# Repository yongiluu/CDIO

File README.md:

# Proyecto CDIO - Sistema de Mando y Control de Vehículo Autónomo / RC

Este repositorio contiene la arquitectura completa de hardware y software para el sistema de control remoto y telemetría de un prototipo vehicular desarrollado bajo la metodología **CDIO** (*Conceive, Design, Implement, Operate*).

El sistema se basa en una arquitectura maestro-esclavo (transmisor-receptor) bidireccional punto a punto (P2P) utilizando dos microcontroladores **ESP32** comunicados mediante el protocolo de baja latencia **ESP-NOW**.

---

## 🚀 Arquitectura General del Sistema

El proyecto está modularizado en dos bloques principales:

```
                  ┌──────────────────────┐
                  │   TRANSMISOR (TX)    │
                  │ (Estación / Control) │
                  └──────────┬───────────┘
                             │  ESP-NOW (WiFi P2P 2.4 GHz)
                             │  Baja Latencia (< 5 ms)
                             ▼
                  ┌──────────────────────┐
                  │    RECEPTOR (RX)     │
                  │   (Vehículo / Auto)  │
                  └──────────┬───────────┘
            ┌────────────────┴────────────────┐
            ▼                                 ▼
   ┌─────────────────┐               ┌─────────────────┐
   │ Servo Dirección │               │  Puente H 43A   │
   │  (Ángulo Turn)  │               │   (BTS7960)     │
   └─────────────────┘               └────────┬────────┘
                                              ▼
                                     ┌─────────────────┐
                                     │  Motor Tracción │
                                     └─────────────────┘
```

1. **`transmisor_TX/` (Estación de Mando / Control Remoto):**
   - Lectura analógica de Joysticks (resolución de 12 bits: `0 - 4095`).
   - Algoritmo de filtrado con **Zona Muerta (Deadzone)** para compensar deriva física (*drift*).
   - Empaquetado de datos en estructura `MensajeDatos` y despacho periódico a alta frecuencia (20 Hz / cada 50 ms).

2. **`receptor_RX/` (Vehículo / Actuadores):**
   - Recepción en tiempo real de paquetes vía callback asíncrono de ESP-NOW.
   - Control de ángulo para servomotor de dirección (`ESP32Servo`, Pin 13).
   - Control de velocidad y sentido de tracción mediante Puente H de alta potencia **BTS7960** (Pines 25, 26 y 27) utilizando canales PWM por hardware (`ledc`).
   - Sistema *Failsafe* (apagado del puente H en reposo para evitar consumo y movimientos involuntarios).

---

## 🛠️ Especificaciones de Hardware y Pines

### 1. Receptor (RX - Vehículo)
* **Microcontrolador:** ESP32-WROOM-32 (esp32dev).
* **Controlador de Tracción:** BTS7960 (43A H-Bridge).
  * `PIN_RPWM` -> **GPIO 25** (Canal PWM 0)
  * `PIN_LPWM` -> **GPIO 26** (Canal PWM 1)
  * `PIN_EN` (R_EN y L_EN unificados) -> **GPIO 27**
  * Potencia limitada a **50 % de PWM** (`PWM_MAX_PCT` en `receptor_RX/src/main.cpp`): el stick a fondo entrega 127 de 255, porque el motor 540 es de 7,2 V y la LiPo 3S llega a 12,6 V.
* **Servomotor de Dirección:** SG90 / MG996R (50 Hz).
  * `PIN_SERVO_DIR` -> **GPIO 13**
* **Sistema de Alimentación:**
  * Batería LiPo 2S/3S conectada a la etapa de potencia del BTS7960 (`B+` y `B-`).
  * Regulador Step-Down DC-DC **LM2596** reduciendo voltaje a 5.0V para alimentar el ESP32 (pin `VIN`/`5V`), el servo y la lógica del BTS7960.
  * Tierras comunes (**GND**) compartidas en un único punto de referencia.

### 2. Transmisor (TX - Control Remoto)
* **Microcontrolador:** ESP32-WROOM-32 (esp32dev).
* **Mando Analógico:** 2 Joysticks analógicos de dos ejes.
  * Eje Y (Velocidad / Tracción) -> **GPIO 34**
  * Eje X (Dirección / Ángulo) -> **GPIO 35**
  * Botón del stick de potencia (*fast brake*) -> **GPIO 25** (pull-down: el otro lado del botón a 3,3 V)
* **Filtrado de Señal:**
  * Rango muerto calibrado entre `1400` y `2000` cuentas ADC para asegurar que el centro físico repose en `Velocidad = 0` y `Ángulo = 90°`.

---

## 📦 Estructura de Datos (ESP-NOW)

Ambas placas intercambian la estructura binaria exacta:

```cpp
typedef struct MensajeDatos {
    int clave;     // 0xCD10: el RX descarta paquetes de otros dispositivos ESP-NOW
    int velocidad; // Rango: -255 a 255 (0 = detenido, >0 = adelante, <0 = reversa)
    int angulo;    // Rango: -38° a +38° del servo respecto al centro (0 = recto; centro en 50°, servo de 12° a 88°)
    int freno;     // 1 = fast brake (click en el stick de potencia)
} MensajeDatos;
```

> Si se cambia esta estructura hay que subir el código al TX **y** al RX: el RX descarta los paquetes de otro tamaño.

### Fast brake
Un click en el stick de potencia activa el freno dinámico: el RX habilita el BTS7960 con `RPWM = LPWM = 0`, lo que pone en corto los bornes del motor a través de los MOSFET inferiores y lo detiene mucho más rápido que en rueda libre. El freno se mantiene al menos 0,5 s y se libera cuando se suelta el botón y el stick vuelve al centro.

---

## ⚙️ Compilación e Instalación

Este proyecto está configurado para **PlatformIO** (extensión recomendada para VS Code). El código compila con el core Arduino-ESP32 2.x y 3.x (por ejemplo `espressif32` 8.0.0 / core 3.3.12): la API `ledc` y los callbacks de ESP-NOW se eligen con `#if` según la versión.

### Pasos de Carga:
1. **Receptor:**
   * Abrir la carpeta `receptor_RX/` en PlatformIO.
   * Compilar y subir el firmware al ESP32 del vehículo.
   * Abrir el Serial Monitor a **115200 baudios** para verificar que imprima su dirección MAC.
2. **Transmisor:**
   * Abrir la carpeta `transmisor_TX/` en PlatformIO.
   * En caso de requerir un cambio de placa, confirmar la MAC de destino en `broadcastAddress`.
   * Compilar y subir el firmware al ESP32 del control remoto.
   * Observar el LED indicador (GPIO 2) que parpadea con cada confirmación de entrega (*ACK*).

---

## 📄 Archivos Adicionales en el Repositorio
* `esquema_electronica.svg`: Esquema de bloques e interconexión de todo el subsistema electrónico y de telecomunicaciones.
* `conexiones esp32.pdf`: Diagrama esquemático de cableado pin a pin de los componentes reales.
* `guardar_como_png.html`: Utilidad para exportar el diagrama de arquitectura en alta resolución.

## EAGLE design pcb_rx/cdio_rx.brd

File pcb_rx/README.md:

# PCB del auto (RX)

Placa de **90 × 60 mm, una capa (Bottom)** que funciona como hub de conexiones: todos los cables entran y salen por borneras de tornillo. Los módulos (ESP32 con su placa de borneras, LM2596 y BTS7960) quedan fuera de la PCB y se conectan con cables. En la PCB solo van las borneras, el conector del servo y los componentes pasivos.

## Archivos

| Archivo | Para qué |
| --- | --- |
| `cdio_rx.brd` | PCB ruteada. En Fusion: **Archivo > Abrir > Abrir desde mi equipo** |
| `cdio_rx.sch` | Esquemático del mismo circuito |
| `cdio_rx_fabricacion.zip` | **Entregable para el CNC**: Gerber del cobre Bottom, contorno, taladros (Excellon) y `LEEME.txt` |
| `fabricacion/` | Los mismos archivos del zip, sin comprimir |
| `generar_pcb.py` | Genera el `.sch` y el `.brd`. Si cambia una medida, se edita aquí y se ejecuta `python generar_pcb.py` |
| `exportar_gerber.py` | Genera los archivos de fabricación y el zip (`python exportar_gerber.py`, requiere shapely) |
| `vista_previa_pcb.png` | Imagen de referencia de la placa |

## Conexiones

| Bornera | Pin | Señal | Va hacia |
| --- | --- | --- | --- |
| J1 BATERIA | 1 / 2 | VBAT / GND | Batería 3S (+ / −), con cable delgado. El motor sigue con su cable grueso directo al BTS7960 |
| J2 LM2596_IN | 1 / 2 | VBAT / GND | Entrada del regulador (IN+ / IN−) |
| J3 LM2596_OUT | 1 / 2 | 5V / GND | Salida del regulador (OUT+ / OUT−), ajustada a 5,0 V |
| J4 ESP32_POWER | 1 / 2 | 5V / GND | Pines 5V y GND de la placa de borneras del ESP32 |
| J5 ESP32_MOTOR | 1 / 2 / 3 | RPWM / LPWM / EN | GPIO 25 / GPIO 26 / GPIO 27 |
| J6 ESP32_SERVO_BAT | 1 / 2 | SERVO / VSENSE | GPIO 13 / GPIO 34 |
| J7 BTS7960_A | de arriba a abajo | RPWM / LPWM / R_EN | Pines RPWM, LPWM y R_EN del BTS7960 |
| J8 BTS7960_B | de arriba a abajo | L_EN / VCC / GND | Pines L_EN, VCC y GND del BTS7960 |
| J9 SERVO | de abajo a arriba | GND / 5V / señal | Enchufe del servo: café / rojo / naranjo |

## Componentes

| Ref. | Valor | Función |
| --- | --- | --- |
| R1 | 56 kΩ | Divisor de batería (lado de VBAT) |
| R2 | 10 kΩ | Divisor de batería (lado de GND) |
| C1 | 100 nF cerámico | Filtra la lectura de batería en GPIO 34 |
| R3, R4, R5 | 10 kΩ | Pull-down de RPWM, LPWM y EN: el motor no se mueve mientras el ESP32 arranca |
| C2 | 1000 µF ≥ 10 V | Reserva para los picos del servo |
| C3 | 100 µF ≥ 10 V | Filtro del 5 V del ESP32 (patas abiertas a 5 mm) |
| J1–J4, J6 | Bornera KF301 de 2 polos, paso 5,08 mm | |
| J5, J7, J8 | Bornera KF301 de 3 polos, paso 5,08 mm | |
| J9 | Tira de 3 pines macho, 2,54 mm | |
| — | 4 tornillos M3 + separadores | Fijación al chasis (agujeros Ø3,2) |

R1, R3 y R4 van acostadas y su cuerpo pasa por encima de otras pistas: así se cruzan señales sin vías en una sola capa.

## Datos para el CNC

- Cobre solo en la capa **Bottom**, con los componentes del lado sin cobre.
- Pistas de 1,0 mm (señales) y 2,0 mm (potencia); separación mínima 0,6 mm.
- El resto del cobre es un plano de GND (aislamiento 0,8 mm), así que hay menos material que fresar.
- Brocas: 1,0 mm (resistencias, condensadores y conector del servo), 1,3 mm (borneras), 3,2 mm (fijación).

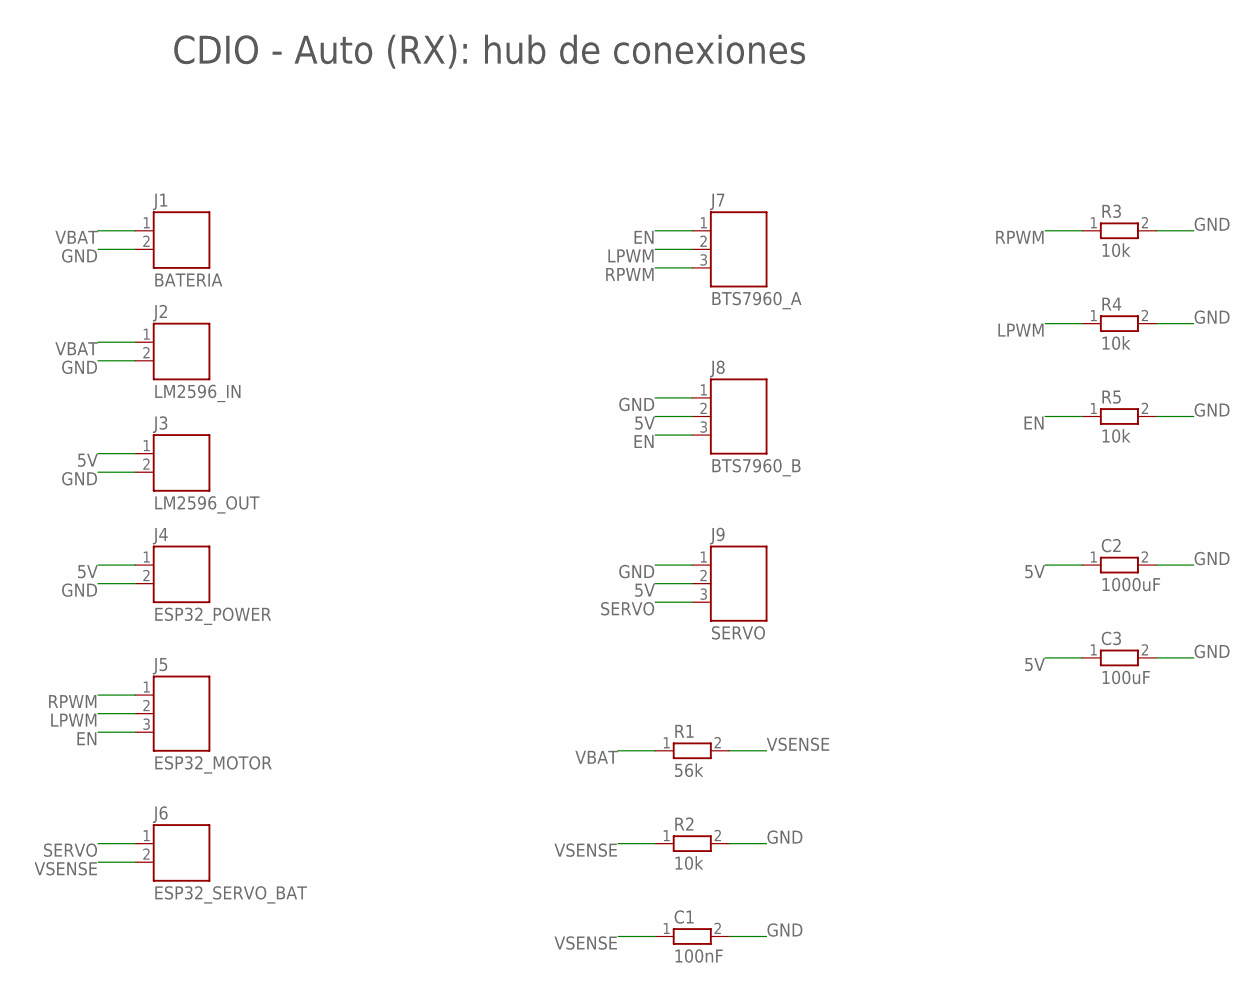
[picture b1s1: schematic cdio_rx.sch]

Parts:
C1: 100nF; C-5
C2: 1000uF; CPOL-5-D10
C3: 100uF; CPOL-5-D8
J1: BATERIA; KF301-2
J2: LM2596_IN; KF301-2
J3: LM2596_OUT; KF301-2
J4: ESP32_POWER; KF301-2
J5: ESP32_MOTOR; KF301-3
J6: ESP32_SERVO_BAT; KF301-2
J7: BTS7960_A; KF301-3
J8: BTS7960_B; KF301-3
J9: SERVO; HDR1X3
R1: 56k; R-0207/15
R2, R5: 10k; R-0207/5V
R3: 10k; R-0207/15
R4: 10k; R-0207/10

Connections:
5V: C2.1 (+), C3.1 (+), J3.1, J4.1, J8.2, J9.2
EN: J5.3, J7.1, J8.3, R5.1
GND: C1.2, C2.2 (-), C3.2 (-), J1.2, J2.2, J3.2, J4.2, J8.1, J9.1, R2.2, R3.2, R4.2, R5.2
LPWM: J5.2, J7.2, R4.1
RPWM: J5.1, J7.3, R3.1
SERVO: J6.1, J9.3
VBAT: J1.1, J2.1, R1.1
VSENSE: C1.1, J6.2, R1.2, R2.1

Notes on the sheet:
CDIO - Auto (RX): hub de conexiones

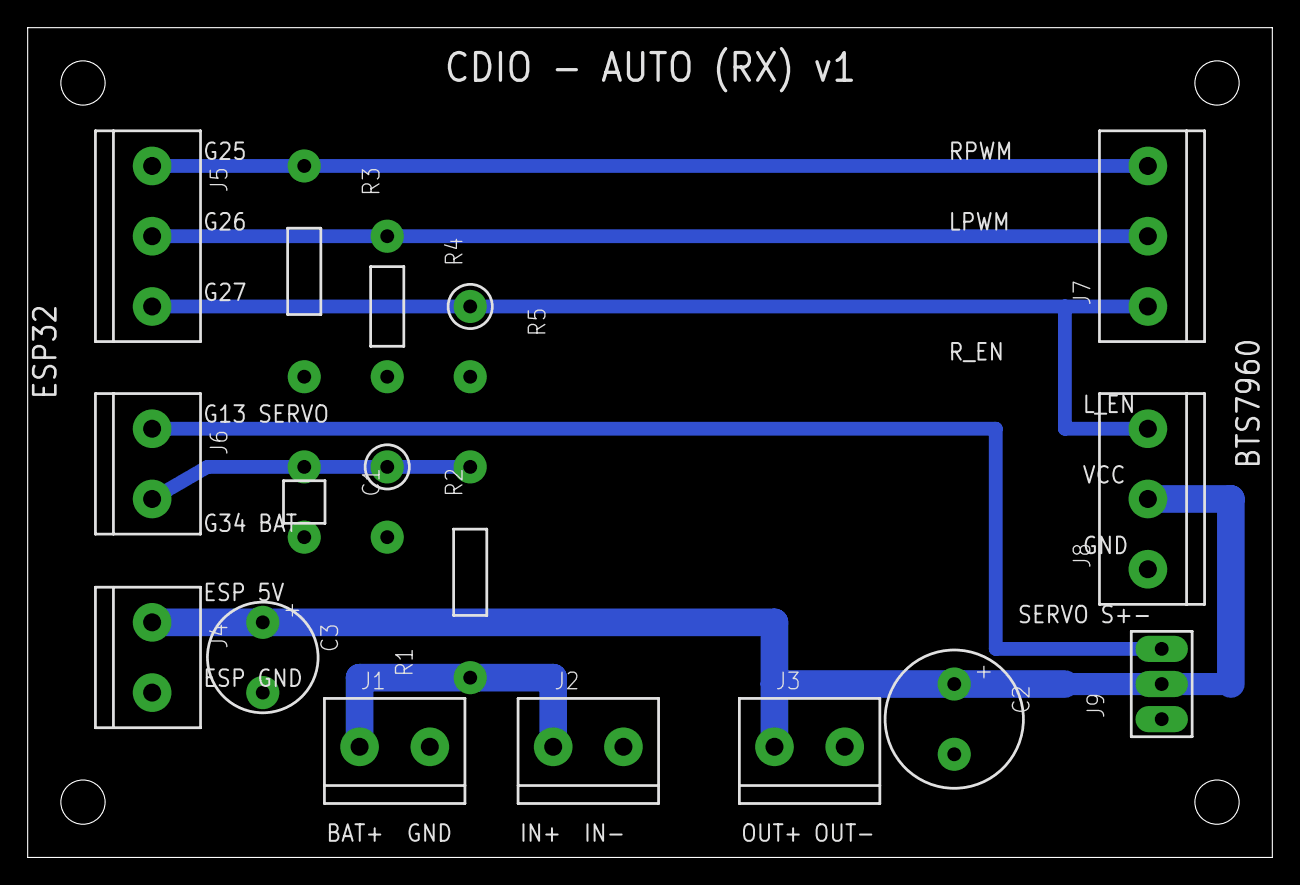
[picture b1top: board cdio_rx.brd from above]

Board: 2 copper layers, 90.0 x 60.0 mm, 17 parts (0 on the bottom side), 8 nets.
